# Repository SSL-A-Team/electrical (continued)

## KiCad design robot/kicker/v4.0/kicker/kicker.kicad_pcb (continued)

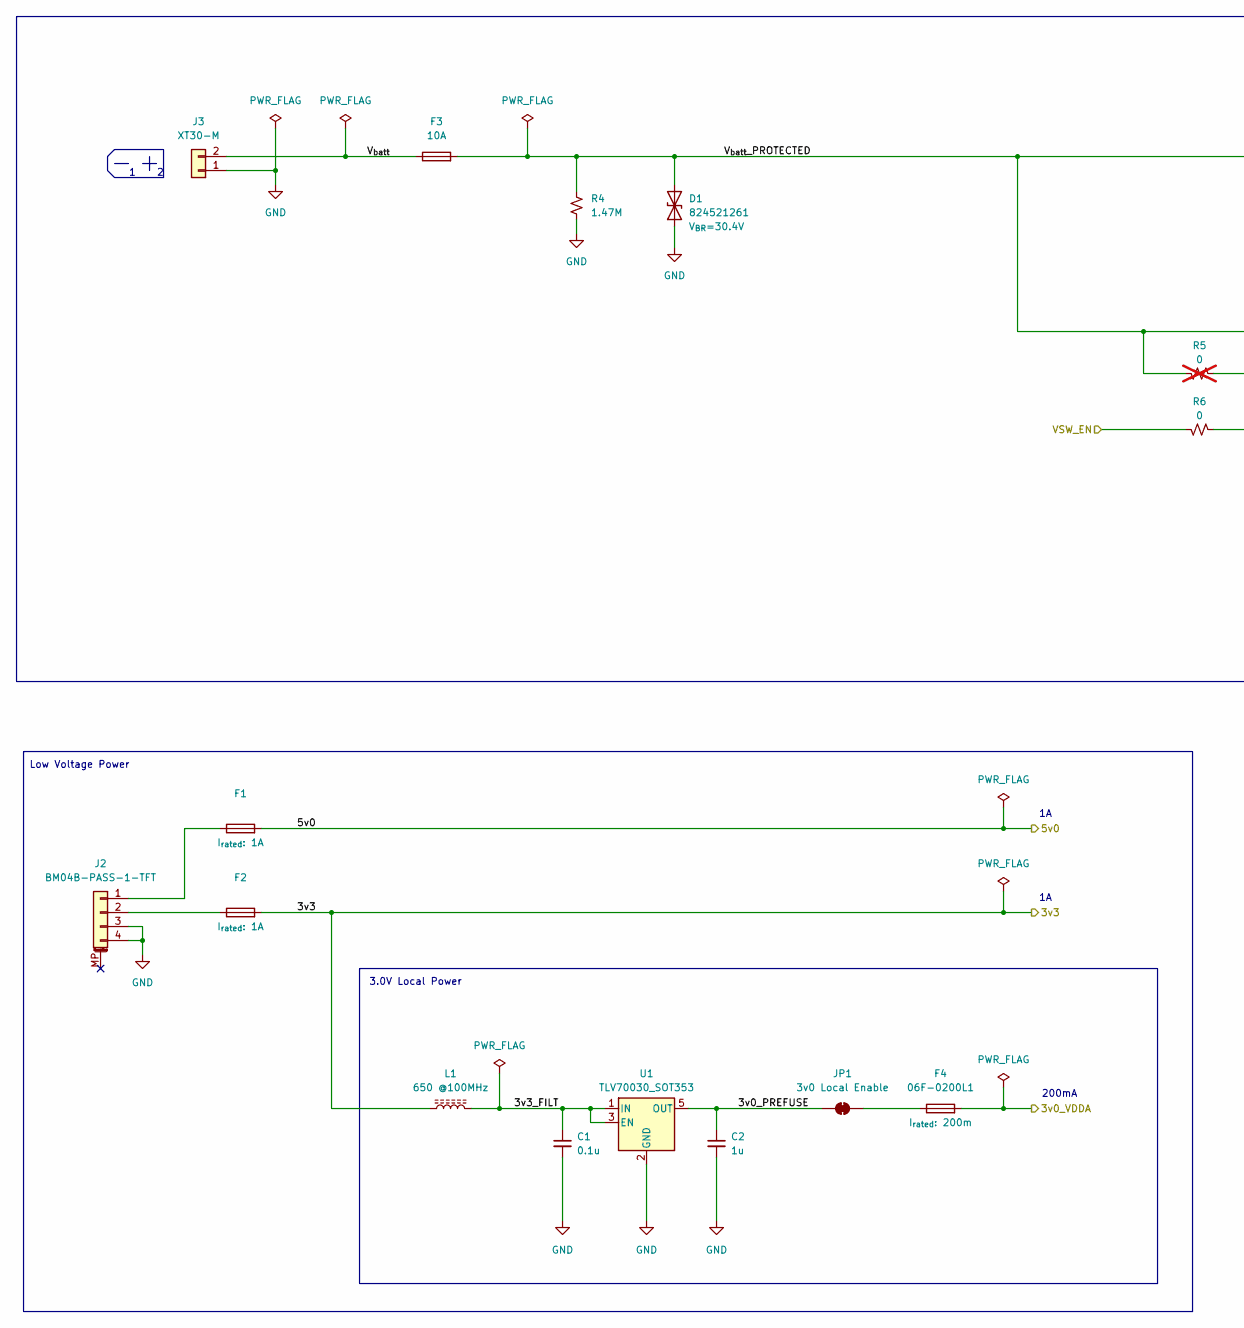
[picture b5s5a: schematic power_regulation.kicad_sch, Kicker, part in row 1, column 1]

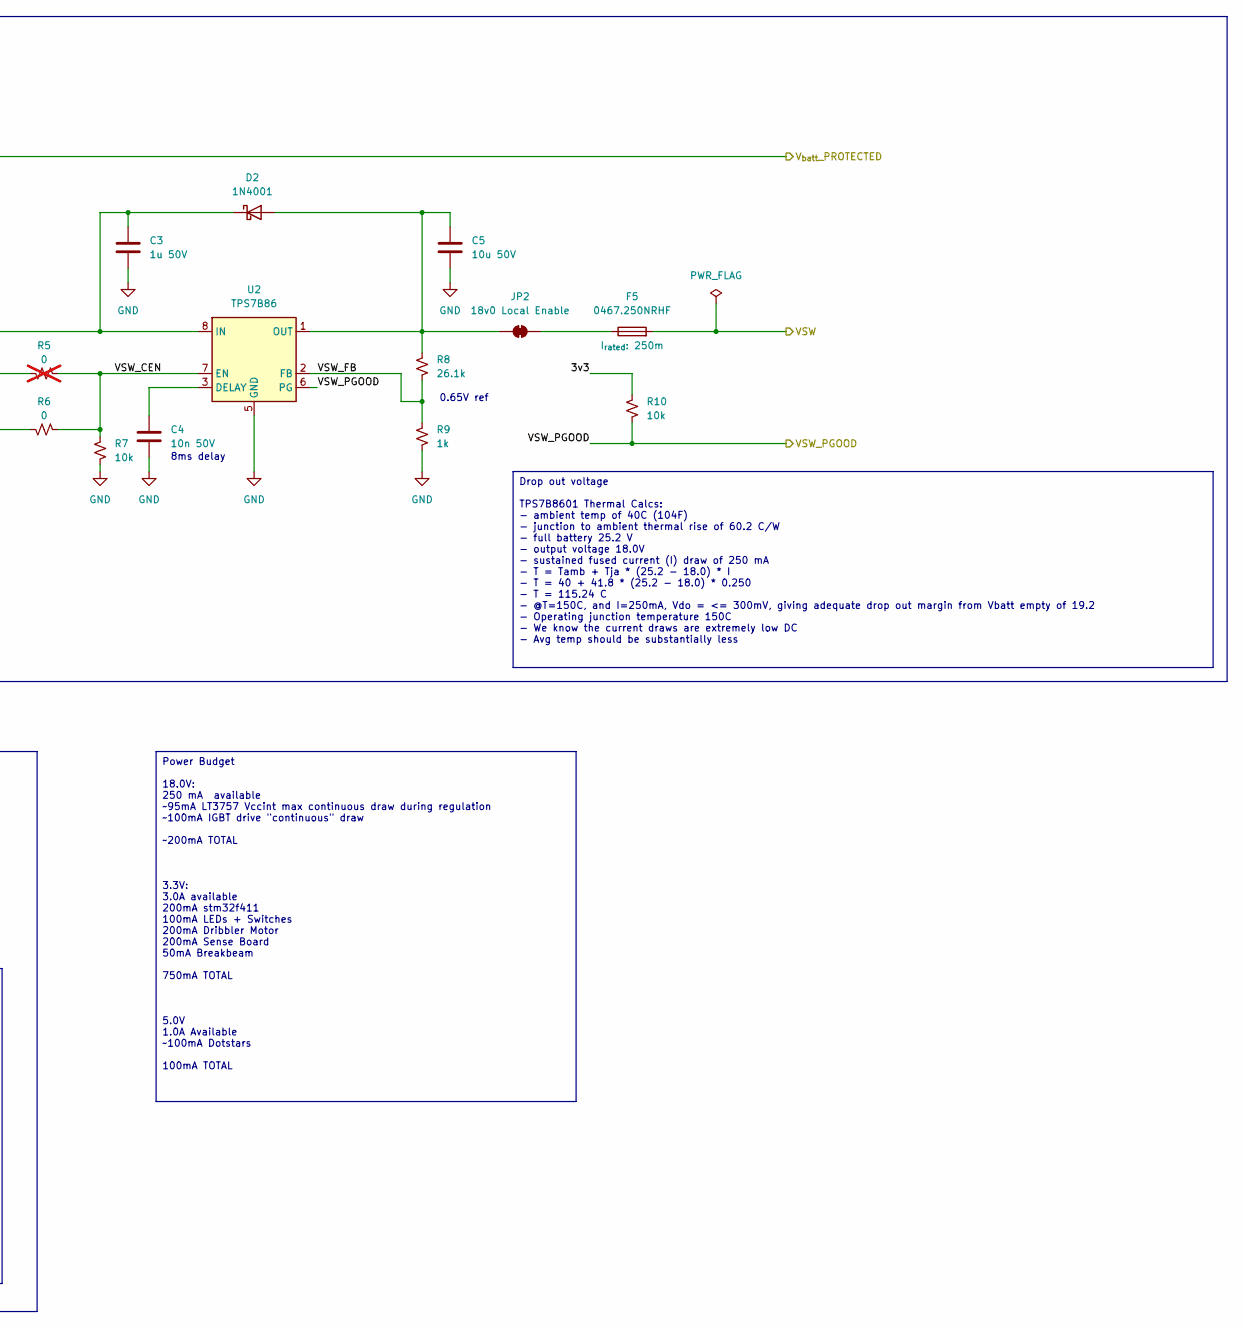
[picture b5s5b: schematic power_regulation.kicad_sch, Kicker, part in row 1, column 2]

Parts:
C1: 0.1u; C_0402_1005Metric; LCSC C307331
C2: 1u; C_1206_3216Metric; LCSC C1848
C3: 1u 50V; C_0402_1005Metric; LCSC C1518208
C4: 10n 50V; C_0402_1005Metric; LCSC C77019
C5: 10u 50V; C_0805_2012Metric; LCSC C440198
D1: 824521261; D_SMB_Non-Polar; LCSC C3708253
D2: 1N4001; D_SMA; LCSC C2909965
F1, F2: Fuse_0603_1608Metric_Pad1.05x0.95mm_HandSolder; LCSC C187605
F3: 10A; 3557-2; LCSC C352820
F4: 06F-0200L1; Fuse_0603_1608Metric_Pad1.05x0.95mm_HandSolder; LCSC C377220
F5: 0467.250NRHF; Fuse_0603_1608Metric_Pad1.05x0.95mm_HandSolder; LCSC C151137
J2: BM04B-PASS-1-TFT; JST_PA_BM04B-PASS_1x04_P2.00_Vertical; LCSC C265298
J3: XT30-M; AMASS_XT30U-M_1x02_P5.0mm_Vertical; LCSC C99102
JP1: 3v0 Local Enable; SolderJumper-2_2.0x1.2mm_Closed
JP2: 18v0 Local Enable; SolderJumper-2_2.0x1.2mm_Closed
L1: 650 @100MHz; R_0603_1608Metric; LCSC C21189
R4: 1.47M; R_0805_2012Metric; LCSC C189666
R5: 0; R_0402_1005Metric; LCSC C106231; not fitted
R6: 0; R_0402_1005Metric; LCSC C106231
R7, R10: 10k; R_0402_1005Metric; LCSC C60490
R8: 26.1k; R_0402_1005Metric; LCSC C102932
R9: 1k; R_0402_1005Metric; LCSC C11702
U1: TLV70030_SOT353; SOT-353_SC-70-5; LCSC C527437
U2: TPS7B86; Texas_HSOP-8-1EP_3.9x4.9mm_P1.27mm; LCSC C5189739

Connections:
+3V0: F4.2; also elsewhere on the board
+3V3: F2.2, L1.1, R10.1; also elsewhere on the board
+5V: F1.2; also elsewhere on the board
+BATT: C3.2, D1.2 (A2), D2.1 (K), F3.2, R4.2, R5.1, U2.8 (IN); also elsewhere on the board
+VSW: F5.2; also elsewhere on the board
/Power Regulation/3v0_PREFUSE: C2.1, JP1.1 (A), U1.5 (OUT)
/Power Regulation/3v3_FILT: C1.1, L1.2, U1.1 (IN), U1.3 (EN)
/Power Regulation/VSW_CEN: R5.2, R6.2, R7.1, U2.7 (EN)
/Power Regulation/VSW_FB: R8.2, R9.1, U2.2 (FB)
/Power Regulation/VSW_PGOOD: R10.2, U2.6 (PG); also elsewhere on the board
/Power Regulation/V_{batt}: F3.1, J3.2
/digital/VSW_EN: R6.1; also elsewhere on the board
GND: C1.2, C2.2, C3.1, C4.2, C5.1, D1.1 (A1), J2.3, J2.4, J3.1, R4.1, R7.2, R9.2, U1.2 (GND), U2.5 (GND), U2.9 (GND); also elsewhere on the board
unnamed: C5.2, D2.2 (A), JP2.1 (A), R8.1, U2.1 (OUT)
unnamed: F1.1, J2.1
unnamed: F2.1, J2.2
unnamed: F4.1, JP1.2 (B)
unnamed: F5.1, JP2.2 (B)
unnamed: C4.1, U2.3 (DELAY)

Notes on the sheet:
Drop out voltage TPS7B8601 Thermal Calcs: - ambient temp of 40C (104F) - junction to ambient thermal rise of 60.2 C/W - full battery 25.2 V - output voltage 18.0V - sustained fused current (I) draw of 250 mA - T = Tamb + Tja * (25.2 - 18.0) * I - T = 40 + 41.8 * (25.2 - 18.0) * 0.250 - T = 115.24 C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
Power Budget 18.0V: 250 mA available ~95mA LT3757 Vccint max continuous draw during regulation ~100mA IGBT drive "continuous" draw ~200mA TOTAL 3.3V: 3.0A available 200mA stm32f411 100mA LEDs + Switches 200mA Dribbler Motor 200mA Sense Board 50mA Breakbeam 750mA TOTAL 5.0V 1.0A Available ~100mA Dot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
0.65V ref
8ms delay
3.0V Local Power
Low Voltage Power
200mA

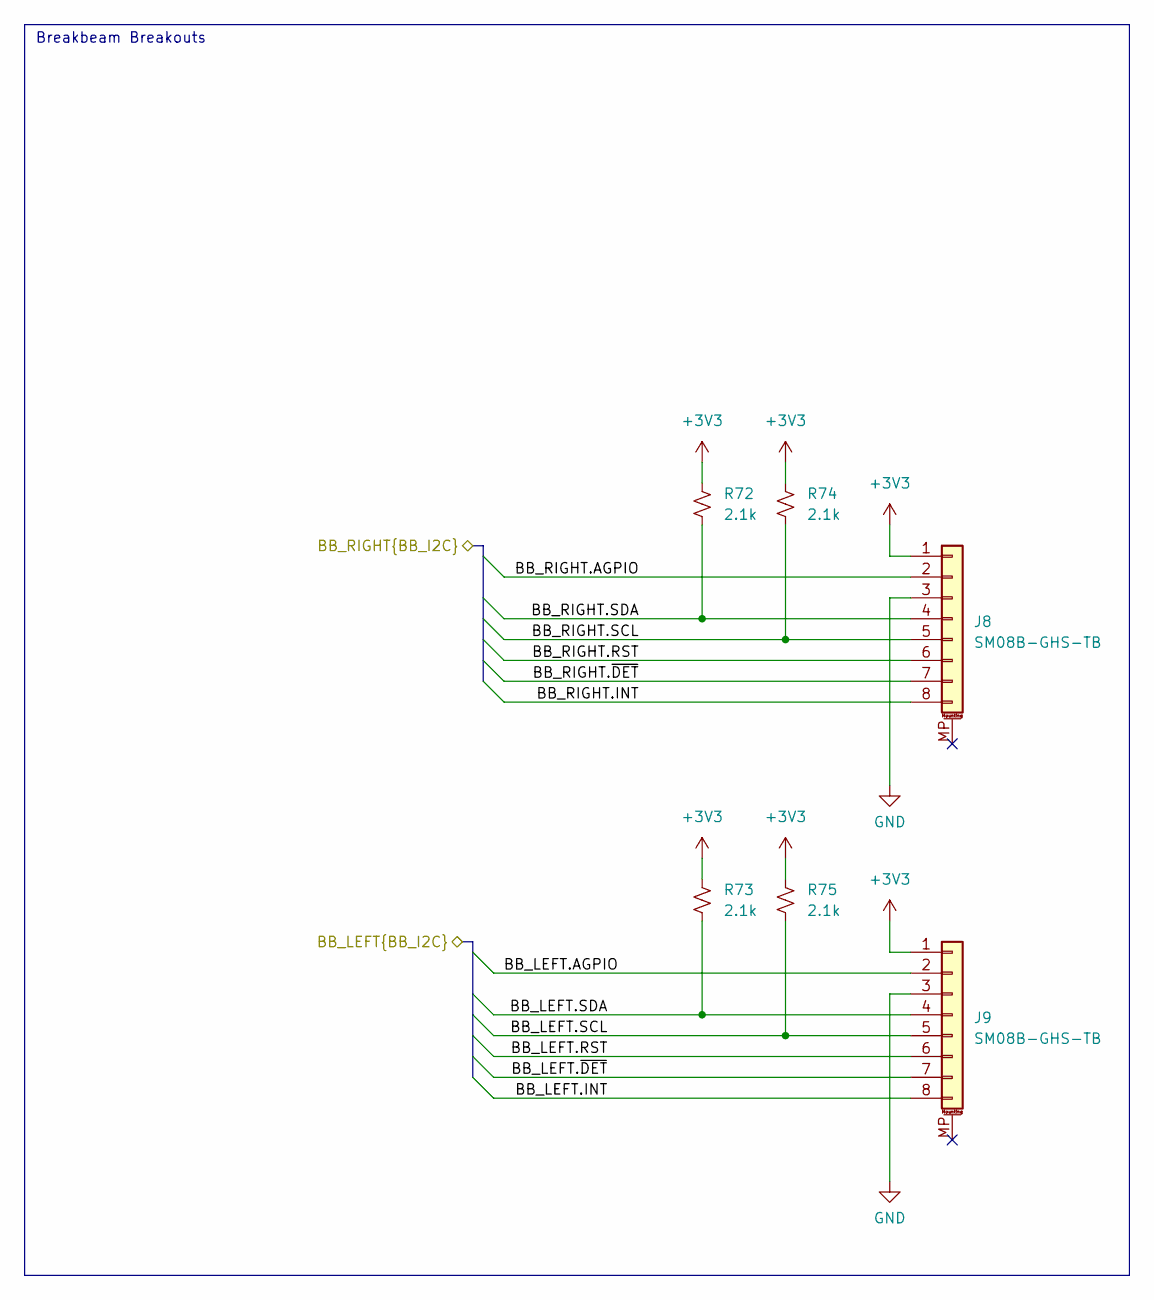
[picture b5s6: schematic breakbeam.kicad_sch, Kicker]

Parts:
J8, J9: SM08B-GHS-TB; JST_GH_SM08B-GHS-TB_1x08-1MP_P1.25mm_Horizontal
R72, R73, R74, R75: 2.1k; R_0402_1005Metric; LCSC C25877

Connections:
+3V3: J8.1, J9.1, R72.1, R73.1, R74.1, R75.1; also elsewhere on the board
/Breakbeam/BB_LEFT.AGPIO: J9.2; also elsewhere on the board
/Breakbeam/BB_LEFT.INT: J9.8; also elsewhere on the board
/Breakbeam/BB_LEFT.RST: J9.6; also elsewhere on the board
/Breakbeam/BB_LEFT.SCL: J9.5, R75.2; also elsewhere on the board
/Breakbeam/BB_LEFT.SDA: J9.4, R73.2; also elsewhere on the board
/Breakbeam/BB_LEFT.~DET: J9.7; also elsewhere on the board
/Breakbeam/BB_RIGHT.AGPIO: J8.2; also elsewhere on the board
/Breakbeam/BB_RIGHT.INT: J8.8; also elsewhere on the board
/Breakbeam/BB_RIGHT.RST: J8.6; also elsewhere on the board
/Breakbeam/BB_RIGHT.SCL: J8.5, R74.2; also elsewhere on the board
/Breakbeam/BB_RIGHT.SDA: J8.4, R72.2; also elsewhere on the board
/Breakbeam/BB_RIGHT.~DET: J8.7; also elsewhere on the board
GND: J8.3, J9.3; also elsewhere on the board

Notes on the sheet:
Breakbeam Breakouts

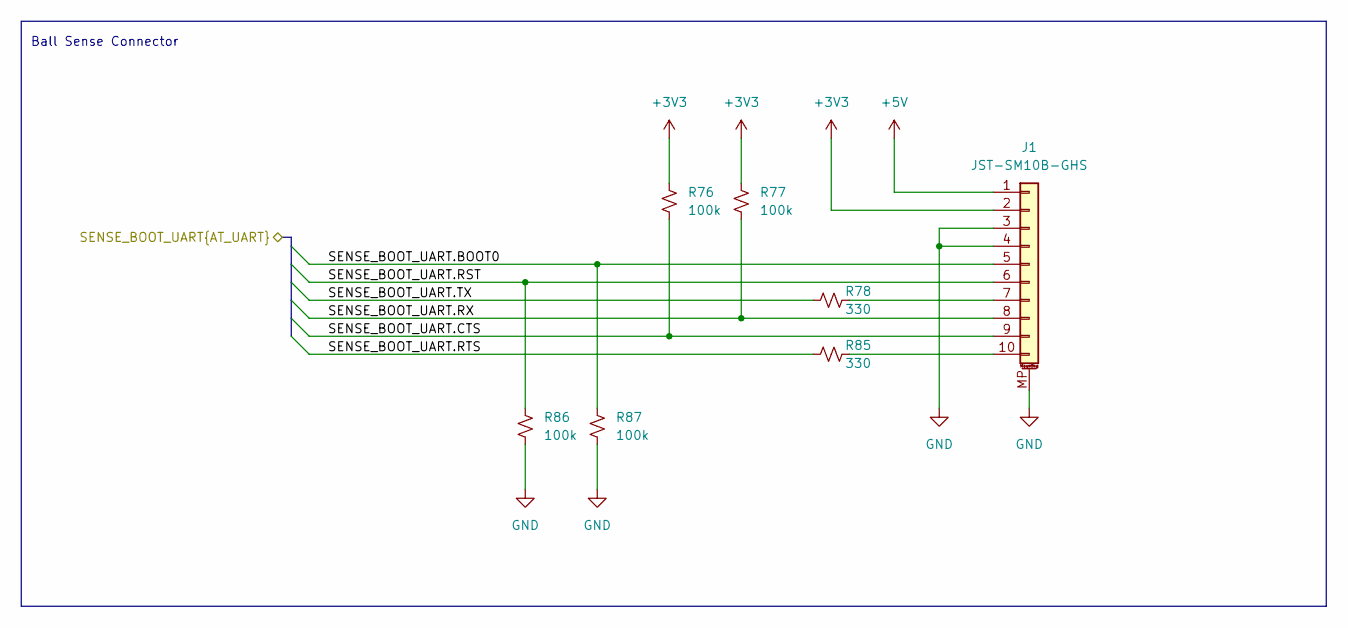
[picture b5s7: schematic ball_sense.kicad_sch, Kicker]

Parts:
J1: JST-SM10B-GHS; JST_GH_SM10B-GHS-TB_1x10-1MP_P1.25mm_Horizontal; LCSC C2683602
R76, R77, R86, R87: 100k; R_0402_1005Metric; LCSC C60491
R78, R85: 330; R_0402_1005Metric; LCSC C105875

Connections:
+3V3: J1.2, R76.1, R77.1; also elsewhere on the board
+5V: J1.1; also elsewhere on the board
/Ball Sense/SENSE_BOOT_UART.BOOT0: J1.5, R87.1; also elsewhere on the board
/Ball Sense/SENSE_BOOT_UART.CTS: J1.9, R76.2; also elsewhere on the board
/Ball Sense/SENSE_BOOT_UART.RST: J1.6, R86.1; also elsewhere on the board
/Ball Sense/SENSE_BOOT_UART.RTS: R85.1; also elsewhere on the board
/Ball Sense/SENSE_BOOT_UART.RX: J1.8, R77.2; also elsewhere on the board
/Ball Sense/SENSE_BOOT_UART.TX: R78.1; also elsewhere on the board
GND: J1.3, J1.4, J1.MP (MountPin), R86.2, R87.2; also elsewhere on the board
unnamed: J1.7, R78.2
unnamed: J1.10, R85.2

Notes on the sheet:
Ball Sense Connector

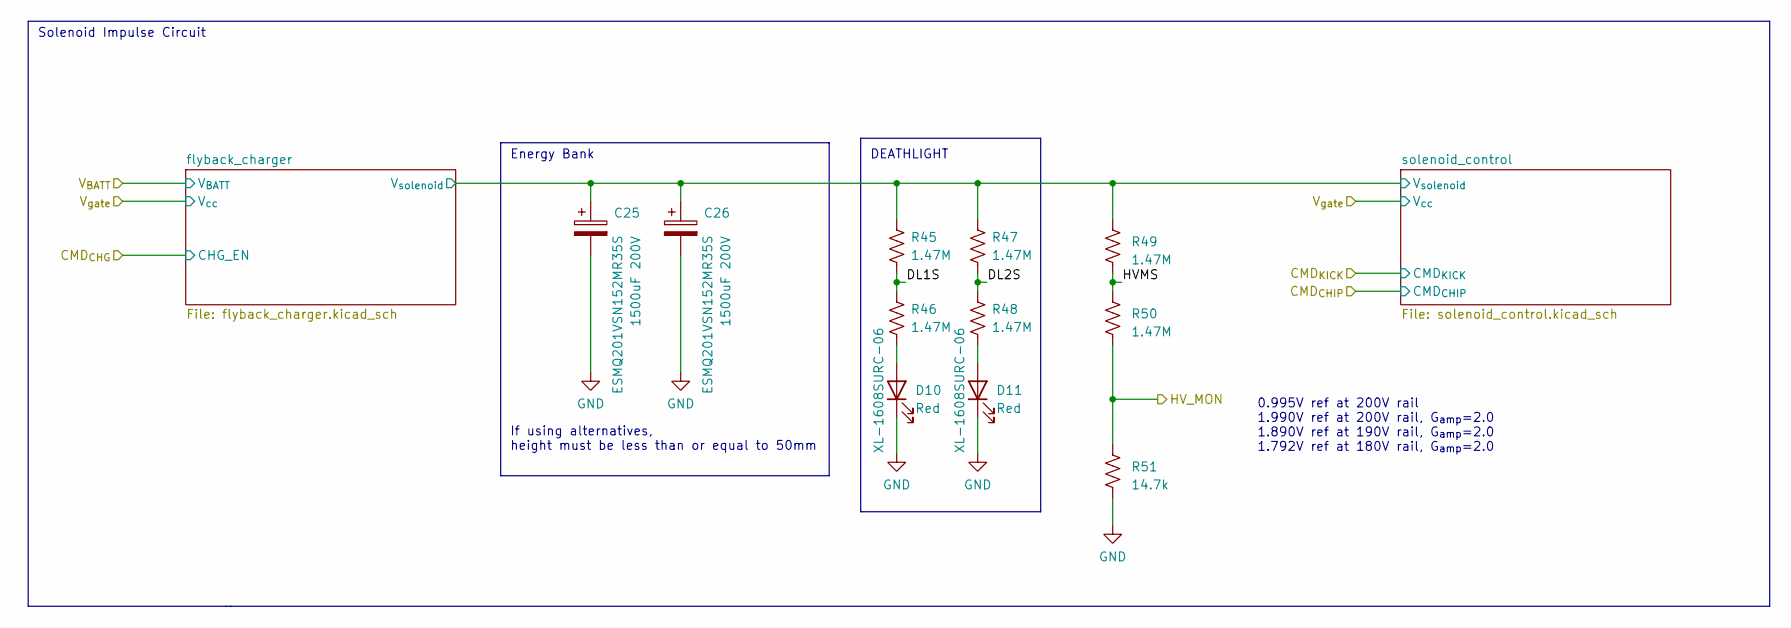
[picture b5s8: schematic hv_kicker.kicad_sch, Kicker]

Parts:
C25, C26: ESMQ201VSN152MR35S; CP_Radial_D30.0mm_P10.00mm_SnapIn
D10, D11: XL-1608SURC-06; LED0603; LCSC C965799
R45, R46, R47, R48, R49, R50: 1.47M; R_0805_2012Metric; LCSC C189666
R51: 14.7k; R_0402_1005Metric; LCSC C25856

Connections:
/digital/V_{sense}_HV: R50.2, R51.1; also elsewhere on the board
/hv_kicker/DL1S: R45.2, R46.1
/hv_kicker/DL2S: R47.2, R48.1
/hv_kicker/HVMS: R49.2, R50.1
/hv_kicker/flyback_charger/V_{solenoid}: C25.1, C26.1, R45.1, R47.1, R49.1; also elsewhere on the board
GND: C25.2, C26.2, D10.1 (K), D11.1 (K), R51.2; also elsewhere on the board
unnamed: D10.2 (A), R46.2
unnamed: D11.2 (A), R48.2

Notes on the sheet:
0.995V ref at 200V rail 1.990V ref at 200V rail, G_{amp}=2.0 1.890V ref at 190V rail, G_{amp}=2.0 1.792V ref at 180V rail, G_{amp}=2.0
Solenoid Impulse Circuit
DEATHLIGHT
Energy Bank
If using alternatives, height must be less than or equal to 50mm

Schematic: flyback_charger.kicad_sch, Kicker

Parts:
C29: REH1020471M050K; CP_Radial_H_InPlane_D10.00mm_H22.00mm_P5.00mm
C30, C32, C33, C36, C38: 10u 50V; C_0805_2012Metric; LCSC C440198
C31: 10n 50V; C_0402_1005Metric; LCSC C77019
C34, C35: 100n 50V; C_0402_1005Metric; LCSC C307331
C37: 6.8n 50V; C_0402_1005Metric; LCSC C93654
C39: 4.7u 50V; C_0805_2012Metric; LCSC C162420
C40: 100n 200V; C_0805_2012Metric; LCSC C784084
C41: 100n 500V; C_1210_3225Metric; LCSC C440207
D14: HS5M; D_SMC; LCSC C2944264
L2: GA3460-BL; GA34XX-BL
Q5: BSC0402NSATMA1; TDSON-8-1
R58: 1k; R_0402_1005Metric; LCSC C11702
R59: 140k; R_0402_1005Metric; LCSC C270645
R60: 22k; R_0402_1005Metric; LCSC C25768
R61: 1; R_0805_2012Metric; LCSC C2907233
R62: 100k; R_0402_1005Metric; LCSC C60491
R63: 10; R_0402_1005Metric; LCSC C138066
R64, R65: PE1206FRM470R008L; R_1206_3216Metric; LCSC C473031
R66, R67: 976k 0.1%; R_0805_2012Metric; LCSC C229056
R68: 17.4k 0.1%; R_0402_1005Metric; LCSC C517755
R88: 0; R_0402_1005Metric; LCSC C106231; not fitted
TP3: CHG_EN; TestPoint_Pad_D1.5mm
TP4: SPICE: V_{drain} <<<HIGH VOLTAGE>>>; TestPoint_Pad_D1.5mm
TP5: FB; TestPoint_Pad_D1.5mm
TP6: SPICE: V_{out} <<<HIGH VOLTAGE>>>; TestPoint_Pad_D1.5mm
U8: LT3757EMSE; MSOP-10-1EP_3x3mm_P0.5mm_EP1.68x1.88mm; LCSC C580135

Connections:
+BATT: C29.1, C30.1, C32.1, C33.1, C35.1, C36.1, C38.1, L2.9, L2.10, L2.11, L2.12, R61.1, U8.10 (VIN); also elsewhere on the board
+VSW: R88.2; also elsewhere on the board
/digital/CMD_{CHG}: R58.1, TP3.1, U8.9 (~SHDN/UVLO); also elsewhere on the board
/hv_kicker/flyback_charger/CSP: Q5.1 (S), Q5.2 (S), Q5.3 (S), R64.2, R65.2, U8.6 (SENSE)
/hv_kicker/flyback_charger/FB: R67.1, R68.2, TP5.1, U8.2 (FBX)
/hv_kicker/flyback_charger/HVFBS: R66.1, R67.2
/hv_kicker/flyback_charger/HVGATE: R62.2, R63.1, U8.7 (GATE)
/hv_kicker/flyback_charger/HV_AC: D14.2 (A), L2.7
/hv_kicker/flyback_charger/V_{solenoid}: C41.1, D14.1 (K), R66.2, TP6.1; also elsewhere on the board
/hv_kicker/flyback_charger/V_{trans}: C40.2, L2.1, L2.2, L2.3, L2.4, Q5.5 (D), TP4.1
GND: C29.2, C30.2, C31.2, C32.2, C33.2, C34.2, C35.2, C36.2, C37.2, C38.2, C39.2, C41.2, L2.6, R58.2, R59.1, R62.1, R64.1, R65.1, R68.1, U8.5 (SYNC), U8.11 (GND); also elsewhere on the board
unnamed: C37.1, R60.1
unnamed: C40.1, R61.2
unnamed: Q5.4 (G), R63.2
unnamed: C39.1, R88.1, U8.8 (INTVCC)
unnamed: R59.2, U8.4 (RT)
unnamed: C31.1, U8.3 (SS)
unnamed: C34.1, R60.2, U8.1 (VC)

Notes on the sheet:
DO NOT blindly copy and modify this schematic according to the datasheet. Spice simulation of this circuit with GA3459 and GA3460 inductors, with leakeage modeled, has shown very high sensitivty to snubber values. Failure to model changes to any core component of the flyback system (transformer, sw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
Switching Freq. 100kHz
High Voltage Regulator
LAYOUT NOTE: LT3751 instructs designs to place fast response decoupling very close the transformer primary to minimize leakage inductance.
Control IO Config
6S LiPo (19.2V-25.2V)
~190.0V-195.0V
12.0V-24.0V
External IO Specs
!!IMPORTANT!!: You must strictly power sequence INTV_{cc} AFTER V_{in}.
V_{logic} nominal, V_{cc} max 100k pull down
Transformer Primary Side Decoupling
RC Snubber

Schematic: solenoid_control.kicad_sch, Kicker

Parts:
C27: 10u 50V; C_0805_2012Metric; LCSC C440198
C28: 100n 50V; C_0402_1005Metric; LCSC C307331
D12, D13: MURS460; D_SMC; LCSC C961891
J5, J6: 2165711002
Q3, Q4: IXGA48N60A3; TO-263-2
R52, R53: 10k; R_0402_1005Metric; LCSC C60490
R54, R55: 100k; R_0402_1005Metric; LCSC C60491
R56, R57: 10; R_0402_1005Metric; LCSC C138066
U7: IX4427; SOIC-8_3.9x4.9mm_P1.27mm; LCSC C171845

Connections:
+VSW: C27.1, C28.1, U7.6 (V+); also elsewhere on the board
/digital/CMD_{CHIP}: R53.1, U7.4 (INB); also elsewhere on the board
/digital/CMD_{KICK}: R52.1, U7.2 (INA); also elsewhere on the board
/hv_kicker/flyback_charger/V_{solenoid}: D12.1 (K), D13.1 (K), J5.1, J6.2; also elsewhere on the board
/hv_kicker/solenoid_control/CHIP_SW: D13.2 (A), J6.1, Q4.2 (C)
/hv_kicker/solenoid_control/GATE_{chip}: R55.1, R57.1, U7.5 (OUTB)
/hv_kicker/solenoid_control/GATE_{chip}_FILT: Q4.1 (G), R57.2
/hv_kicker/solenoid_control/GATE_{kick}: R54.1, R56.1, U7.7 (OUTA)
/hv_kicker/solenoid_control/GATE_{kick}_FILT: Q3.1 (G), R56.2
/hv_kicker/solenoid_control/KICK_SW: D12.2 (A), J5.2, Q3.2 (C)
GND: C27.2, C28.2, Q3.3 (E), Q4.3 (E), R52.2, R53.2, R54.2, R55.2, U7.3 (GND); also elsewhere on the board

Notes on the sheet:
Solenoid DC Resistance Must be >= 1.7 Ohms
IGBT Driver
12.0V-20.0V
V_{logic}, 100k pull down
External IO Specs
Discharge Circuit
Package_TO_SOT_THT:TO-247-3_Horizontal_TabDown: IXXH110N65C4 D2PAK: IXGA48N60A3-TRL 120A 600V
<=250.0V
V_{logic} = 3.3V nominal (1.8V-V_{cc})

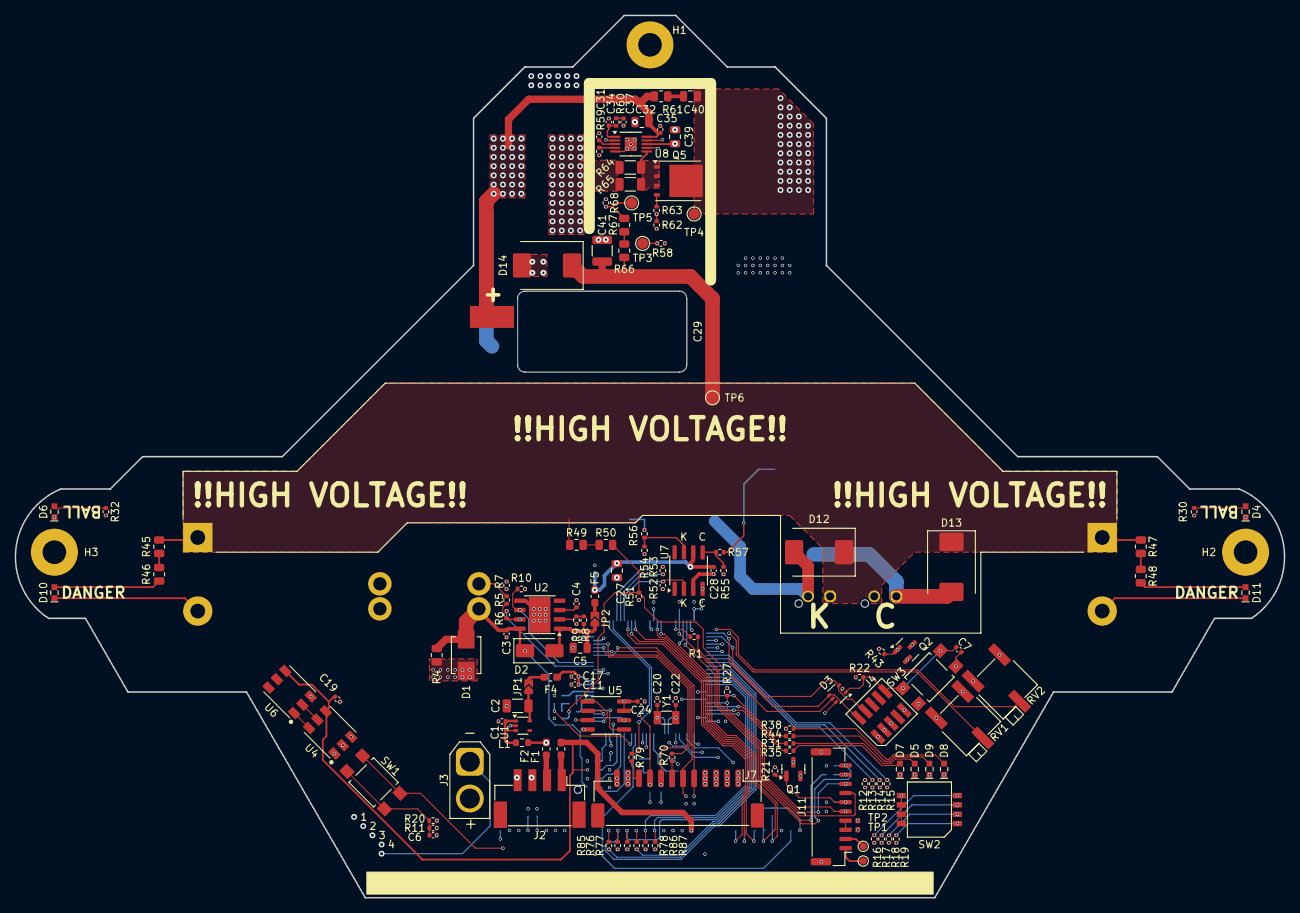
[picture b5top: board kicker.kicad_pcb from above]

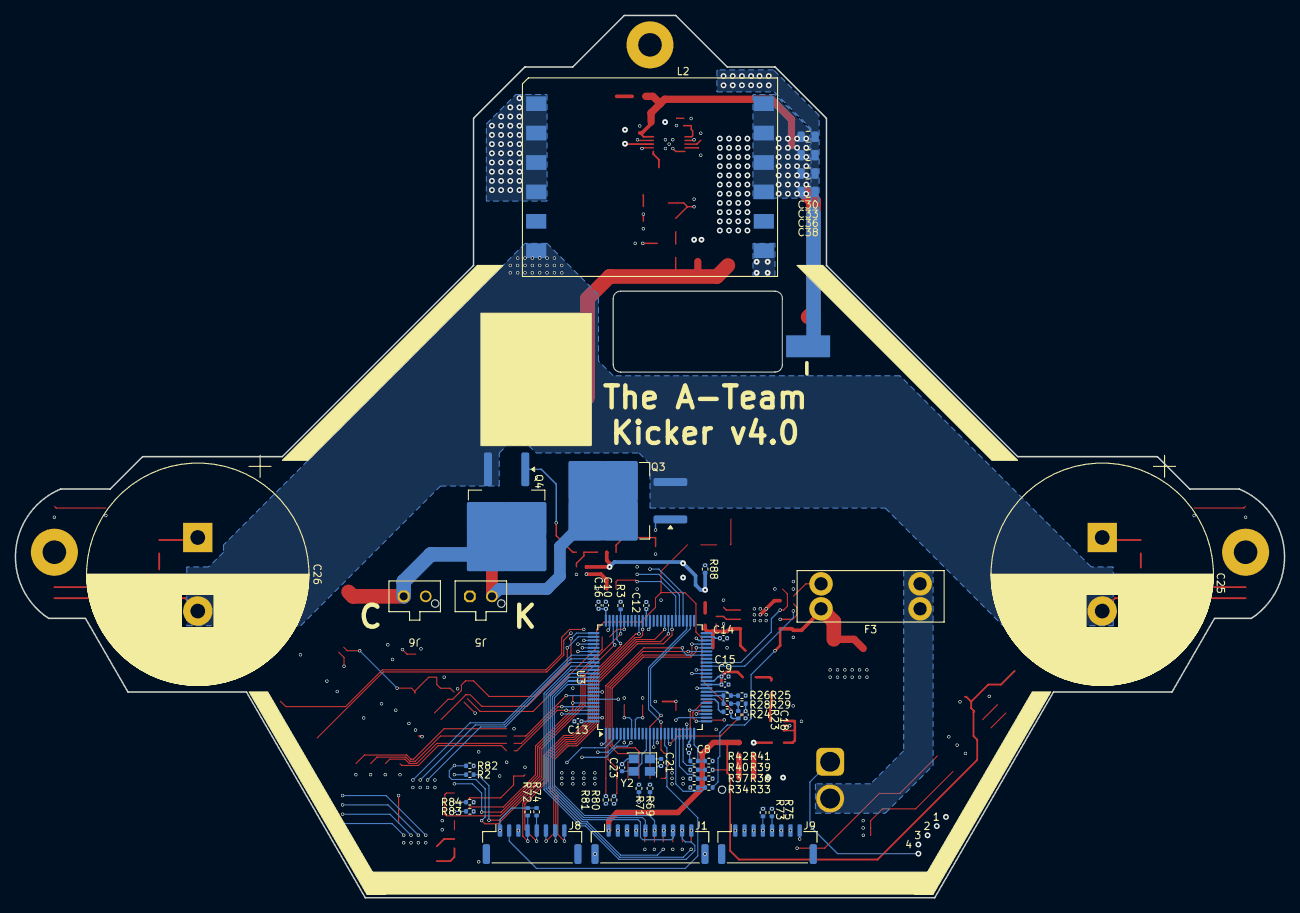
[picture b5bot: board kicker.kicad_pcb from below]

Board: 6 copper layers, 172.6 x 120.0 mm, 191 parts (56 on the bottom side), 134 nets.

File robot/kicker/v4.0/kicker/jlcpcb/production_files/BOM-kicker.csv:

Comment,Designator,Footprint,LCSC,Quantity
26.1k,R8,R_0402_1005Metric,C102932,1
330,"R1,R12,R13,R14,R15,R2,R20,R70,R78,R79,R85",R_0402_1005Metric,C105875,11
0,"R24,R28,R6",R_0402_1005Metric,C106231,3
1k,"R29,R34,R37,R40,R42,R58,R9",R_0402_1005Metric,C11702,7
10,"R56,R57,R63",R_0402_1005Metric,C138066,3
0467.250NRHF,F5,Fuse_0603_1608Metric_Pad1.05x0.95mm_HandSolder,C151137,1
1u 50V,"C11,C17,C3",C_0402_1005Metric,C1518208,3
11pF,"C21,C23",C_0402_1005Metric,C161525,2
4.7u 50V,C39,C_0805_2012Metric,C162420,1
23.2k,R38,R_0402_1005Metric,C163477,1
1u,C2,C_1206_3216Metric,C1848,1
~,"F1,F2",Fuse_0603_1608Metric_Pad1.05x0.95mm_HandSolder,C187605,2
1.47M,"R4,R45,R46,R47,R48,R49,R50",R_0805_2012Metric,C189666,7
650 @100MHz,L1,R_0603_1608Metric,C21189,1
976k 0.1%,"R66,R67",R_0805_2012Metric,C229056,2
BSS138K,"Q1,Q2",SOT-23,C255592,2
22k,R60,R_0402_1005Metric,C25768,1
14.7k,R51,R_0402_1005Metric,C25856,1
1.5k,R39,R_0402_1005Metric,C25867,1
2.1k,"R72,R73,R74,R75",R_0402_1005Metric,C25877,4
SM08B-GHS-TB,"J8,J9",JST_GH_SM08B-GHS-TB_1x08-1MP_P1.25mm_Horizontal,C265111,2
BM04B-PASS-1-TFT,J2,JST_PA_BM04B-PASS_1x04_P2.00_Vertical,C265298,1
JST-SM10B-GHS,"J1,J11",JST_GH_SM10B-GHS-TB_1x10-1MP_P1.25mm_Horizontal,C2683602,2
140k,R59,R_0402_1005Metric,C270645,1
11.5k,R33,R_0402_1005Metric,C270653,1
8.06k,R36,R_0402_1005Metric,C276278,1
SK9822,"U4,U6",SK9822,C2829089,2
BTN0,"SW1,SW3",SW_SPST_TL3305A,C2886902,2
1,R61,R_0805_2012Metric,C2907233,1
1N4001,D2,D_SMA,C2909965,1
HS5M,D14,D_SMC,C2944264,1
0.1u,"C1,C10,C12,C13,C14,C15,C16,C18,C24,C28,C34,C35,C6,C7",C_0402_1005Metric,C307331,14
10A,F3,3557-2,C352820,1
824521261,D1,D_SMB_Non-Polar,C3708253,1
06F-0200L1,F4,Fuse_0603_1608Metric_Pad1.05x0.95mm_HandSolder,C377220,1
TAXM8M4RDBCCT2T,Y2,Crystal_SMD_3225-4Pin_3.2x2.5mm,C400090,1
STM32G474VETx,U3,LQFP-100_14x14mm_P0.5mm,C431632,1
10u 50V,"C27,C30,C32,C33,C36,C38,C5",C_0805_2012Metric,C440198,7
100n 500V,C41,C_1210_3225Metric,C440207,1
Conn_ARM_JTAG_SWD_10,J4,Samtec-2x5pin-1.27mm,C448647,1
PE1206FRM470R008L,"R64,R65",R_1206_3216Metric,C473031,2
PESD3V3L5UY,D3,SOT-363_SC-70-6,C477992,1
17.4k 0.1%,R68,R_0402_1005Metric,C517755,1
TPS7B86,U2,Texas_HSOP-8-1EP_3.9x4.9mm_P1.27mm,C5189739,1
TLV70030_SOT353,U1,SOT-353_SC-70-5,C527437,1
LT3757EMSE,U8,MSOP-10-1EP_3x3mm_P0.5mm_EP1.68x1.88mm,C580135,1
IX4427,U7,SOIC-8_3.9x4.9mm_P1.27mm,C5804604,1
10k,"R10,R11,R16,R17,R18,R19,R25,R26,R27,R30,R31,R32,R35,R43,R44,R52,R53,R7",R_0402_1005Metric,C60490,18
100k,"R21,R3,R54,R55,R62,R69,R71,R76,R77,R80,R81,R82,R83,R84,R86,R87",R_0402_1005Metric,C60491,16
4.7u 6.3V,"C19,C8",C_0402_1005Metric,C76995,2
10n 50V,"C31,C4,C9",C_0402_1005Metric,C77019,3
100n 200V,C40,C_0805_2012Metric,C784084,1
649,R41,R_0402_1005Metric,C82294,1
Q13FC13500005,Y1,Crystal_SMD_3215-2Pin_3.2x1.5mm,C841881,1
15pF,"C20,C22",C_0402_1005Metric,C88877,2
6.8n 50V,C37,C_0402_1005Metric,C93654,1
MURS460,"D12,D13",D_SMC,C961891,2
XL-1608SURC-06,"D10,D11,D7",LED0603,C965799,3
XL-1608UOC-06,D9,LED0603,C965800,1
XL-1608UGC-04,D5,LED0603,C965804,1
XL-1608UBC-04,"D4,D6",LED0603,C965807,2
XL-1608UWC-04,D8,LED0603,C965808,1
5v0 US,TP1,TestPoint_Pad_D1.0mm,,1
2165711002,J6,2165711002,,1
2165711002,J5,2165711002,,1
ESMQ201VSN152MR35S,C26,CP_Radial_D30.0mm_P10.00mm_SnapIn,,1
ESMQ201VSN152MR35S,C25,CP_Radial_D30.0mm_P10.00mm_SnapIn,,1
GA3460-BL,L2,GA34XX-BL,,1
IXGA48N60A3,Q3,TO-263-2,,1
IXGA48N60A3,Q4,TO-263-2,,1
3v3 US,TP2,TestPoint_Pad_D1.0mm,,1
SW_DIP_x04,SW2,CHP-041TB,,1
BSC0402NSATMA1,Q5,TDSON-8-1,,1
REH1020471M050K,C29,CP_Radial_H_InPlane_D10.00mm_H22.00mm_P5.00mm,,1
3269P-1-103GLF,RV1,Potentiometer_Bourns_3269P_Horizontal,,1
3269P-1-103GLF,RV2,Potentiometer_Bourns_3269P_Horizontal,,1
SM12B-ZESS-TB,J7,JST_ZE_BM12B-ZESS-TBT_1x12-1MP_P1.50mm_Vertical,,1

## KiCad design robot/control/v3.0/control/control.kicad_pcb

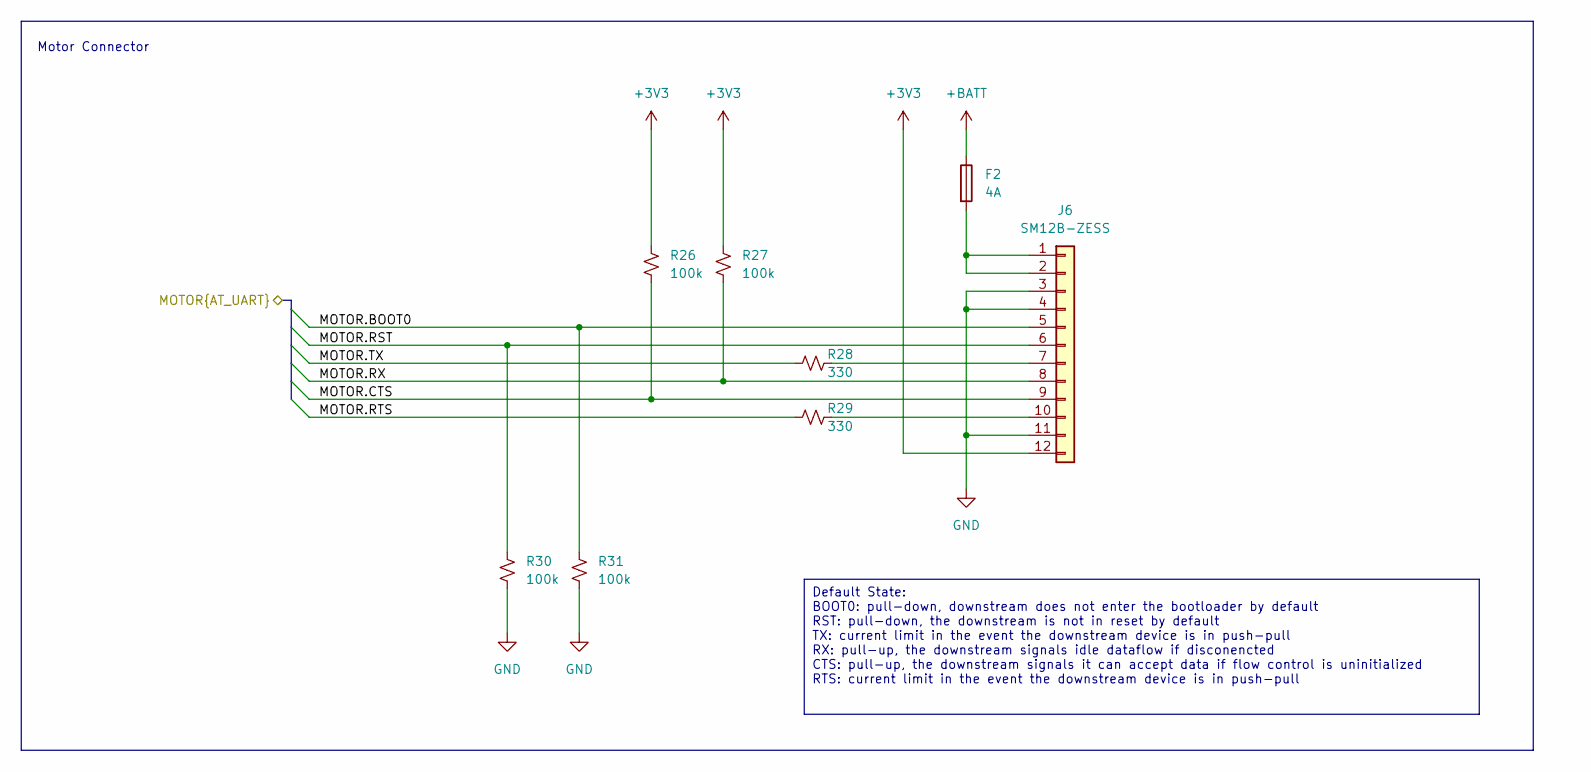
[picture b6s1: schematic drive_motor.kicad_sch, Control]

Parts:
F2: 4A; Fuse_1206_3216Metric_Pad1.42x1.75mm_HandSolder
J6: SM12B-ZESS; JST_ZE_SM12B-ZESS-TB_1x12-1MP_P1.50mm_Horizontal
R26, R27, R30, R31: 100k; R_0402_1005Metric
R28, R29: 330; R_0402_1005Metric

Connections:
+3V3: J6.12, R26.1, R27.1; also elsewhere on the board
+BATT: F2.1; also elsewhere on the board
/back_right_drive_motor/MOTOR.BOOT0: J6.5, R31.1; also elsewhere on the board
/back_right_drive_motor/MOTOR.CTS: J6.9, R26.2; also elsewhere on the board
/back_right_drive_motor/MOTOR.RST: J6.6, R30.1; also elsewhere on the board
/back_right_drive_motor/MOTOR.RTS: R29.1; also elsewhere on the board
/back_right_drive_motor/MOTOR.RX: J6.8, R27.2; also elsewhere on the board
/back_right_drive_motor/MOTOR.TX: R28.1; also elsewhere on the board
GND: J6.3, J6.4, J6.11, R30.2, R31.2; also elsewhere on the board
unnamed: F2.2, J6.1, J6.2
unnamed: J6.7, R28.2
unnamed: J6.10, R29.2

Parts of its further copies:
F1, F3, F4: 4A; Fuse_1206_3216Metric_Pad1.42x1.75mm_HandSolder
J3, J7, J8: SM12B-ZESS; JST_ZE_SM12B-ZESS-TB_1x12-1MP_P1.50mm_Horizontal
R16, R17, R20, R21, R32, R33, R36, R37, R38, R39, R42, R43: 100k; R_0402_1005Metric
R18, R19, R34, R35, R40, R41: 330; R_0402_1005Metric

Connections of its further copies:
+3V3: J3.12, J7.12, J8.12, R16.1, R17.1, R32.1, R33.1, R38.1, R39.1; also elsewhere on the board
+BATT: F1.1, F3.1, F4.1; also elsewhere on the board
/back_left_drive_motor/MOTOR.BOOT0: J7.5, R37.1; also elsewhere on the board
/back_left_drive_motor/MOTOR.CTS: J7.9, R32.2; also elsewhere on the board
/back_left_drive_motor/MOTOR.RST: J7.6, R36.1; also elsewhere on the board
/back_left_drive_motor/MOTOR.RTS: R35.1; also elsewhere on the board
/back_left_drive_motor/MOTOR.RX: J7.8, R33.2; also elsewhere on the board
/back_left_drive_motor/MOTOR.TX: R34.1; also elsewhere on the board
/front_left_drive_motor/MOTOR.BOOT0: J8.5, R43.1; also elsewhere on the board
/front_left_drive_motor/MOTOR.CTS: J8.9, R38.2; also elsewhere on the board
/front_left_drive_motor/MOTOR.RST: J8.6, R42.1; also elsewhere on the board
/front_left_drive_motor/MOTOR.RTS: R41.1; also elsewhere on the board
/front_left_drive_motor/MOTOR.RX: J8.8, R39.2; also elsewhere on the board
/front_left_drive_motor/MOTOR.TX: R40.1; also elsewhere on the board
/front_right_drive_motor/MOTOR.BOOT0: J3.5, R21.1; also elsewhere on the board
/front_right_drive_motor/MOTOR.CTS: J3.9, R16.2; also elsewhere on the board
/front_right_drive_motor/MOTOR.RST: J3.6, R20.1; also elsewhere on the board
/front_right_drive_motor/MOTOR.RTS: R19.1; also elsewhere on the board
/front_right_drive_motor/MOTOR.RX: J3.8, R17.2; also elsewhere on the board
/front_right_drive_motor/MOTOR.TX: R18.1; also elsewhere on the board
GND: J3.3, J3.4, J3.11, J7.3, J7.4, J7.11, J8.3, J8.4, J8.11, R20.2, R21.2, R36.2, R37.2, R42.2, R43.2; also elsewhere on the board
unnamed: F1.2, J3.1, J3.2
unnamed: J3.7, R18.2
unnamed: J3.10, R19.2
unnamed: F3.2, J7.1, J7.2
unnamed: J7.7, R34.2
unnamed: J7.10, R35.2
unnamed: F4.2, J8.1, J8.2
unnamed: J8.7, R40.2
unnamed: J8.10, R41.2

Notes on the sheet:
Default State: BOOT0: pull-down, downstream does not enter the bootloader by default RST: pull-down, the downstream is not in reset by default TX: current limit in the event the downstream device is in push-pull RX: pull-up, the downstream signals idle dataflow if disconencted CTS: pull-up, the dow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
Motor Connector
